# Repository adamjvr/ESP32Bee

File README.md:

# ESP32Bee
An ESP32 module in the XBee Formfactor
- XBee 2mm pitch headers, same pinout slightly modified
- ESP32 WiFi/BLE Dual Core Microcontroll/SoC
- UM Antenna Connector for external 2.4GHZ Antennas
- Open Source Hardware under CERN License
- Designed In KiCAD

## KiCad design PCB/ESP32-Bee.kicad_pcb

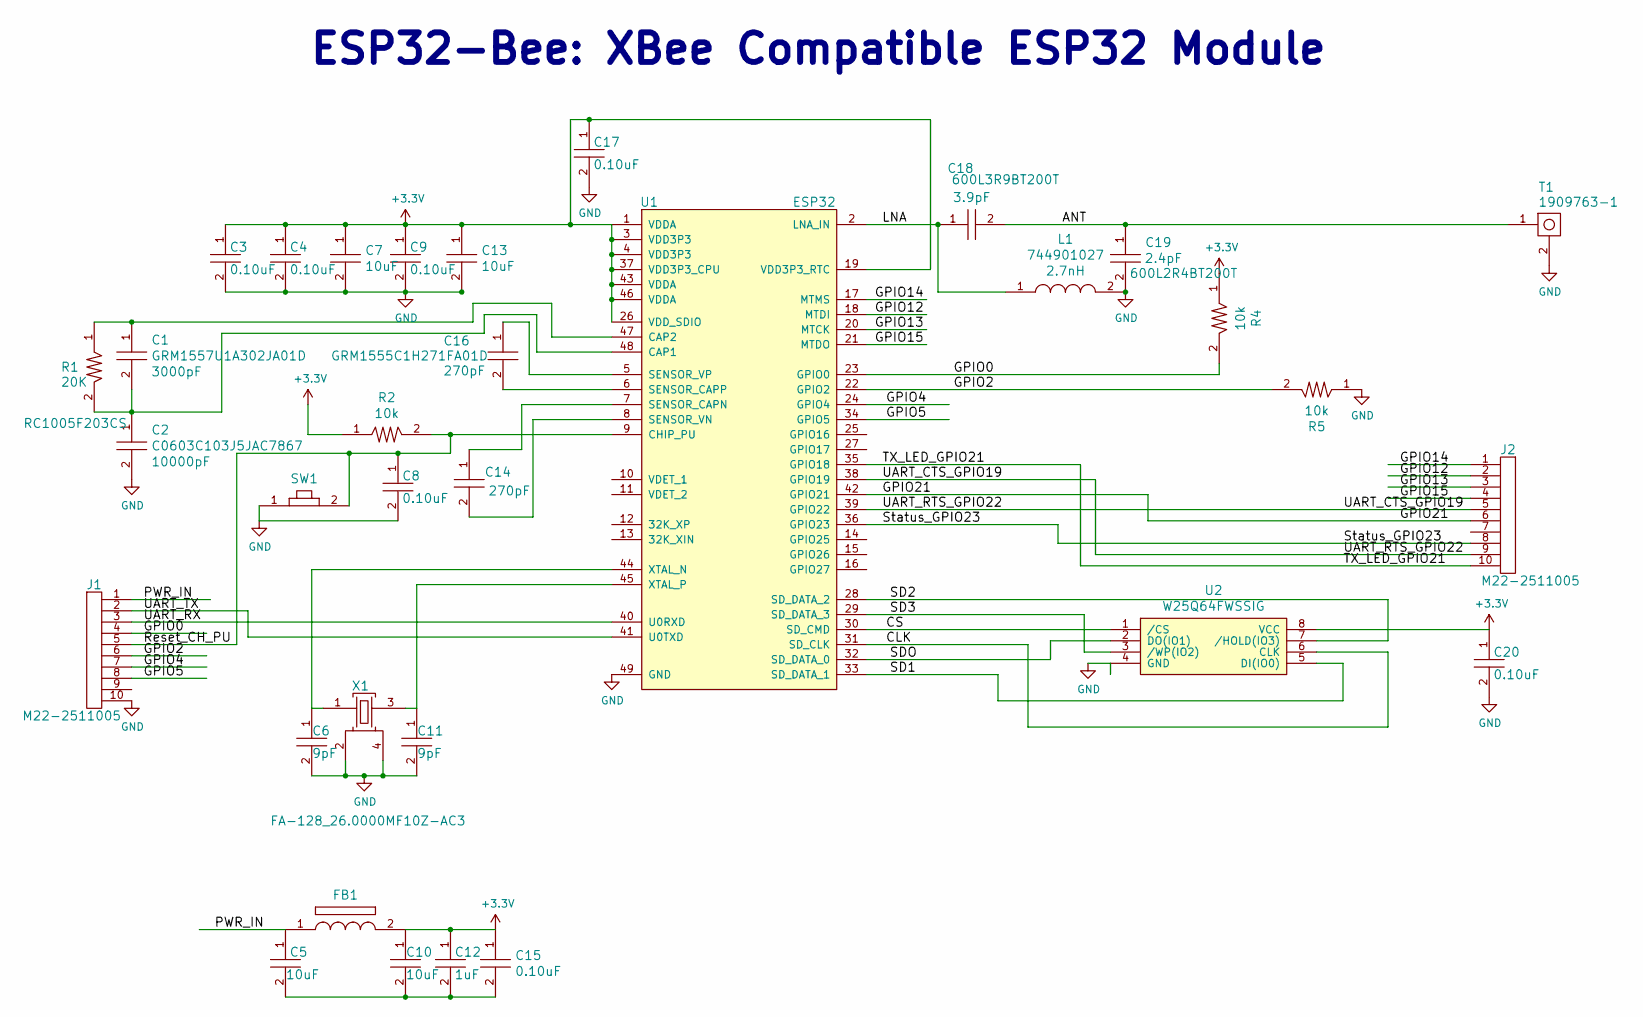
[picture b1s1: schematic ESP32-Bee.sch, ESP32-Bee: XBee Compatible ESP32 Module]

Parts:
C1: GRM1557U1A302JA01D; C0402; Tolerance 0.1pF; Voltage 10V; MFR# GRM1557U1A302JA01D
C2: C0603C103J5JAC7867; C0603; Tolerance 5%; Voltage 50V; MFR# C0603C103J5JAC7867
C3, C4, C8, C9, C15, C17, C20: CL05B104JP5NNNC; C0402; Tolerance 5%; Voltage 10V; MFR# CL05B104JP5NNNC
C5, C7, C10, C13: CL10A106KQ8NNNC; C0603; Tolerance 10%; Voltage 6.3V; MFR# CL10A106KQ8NNNC
C6, C11: CL05C090CB5NNNC; C0402; Tolerance 0.25pF; Voltage 50V; MFR# CL05C090CB5NNNC
C12: CL05A105KA5NQNC; C0402; Tolerance 10%; Voltage 25V; MFR# CL05A105KA5NQNC
C14, C16: GRM1555C1H271FA01D; C0402; Tolerance 270pF; Voltage 50V; MFR# GRM1557U1A302JA01D
C18: 600L3R9BT200T; C0402; Tolerance 0.1pF; Voltage 200V; MFR# 600L3R9BT200T
C19: 600L2R4BT200T; C0402; Tolerance 2.4pF; Voltage 200V; MFR# 600L2R4BT200T
FB1: MI0603K300R-10; Tolerance N/A; Voltage N/A; MFR# MI0603K300R-10
J1, J2: M22-2511005; Tolerance N/A; Voltage N/A; MFR# M22-2511005
L1: 744901027; BLM15HG601SN1D; Tolerance 0.1nH; Voltage N/A; MFR# 744901027
R1: RC1005F203CS; R0402; Tolerance 1%; Voltage N/A; MFR# RC1005F103CS
R2, R4, R5: RC1005F103CS; R0402; Tolerance 1%; Voltage N/A; MFR# RC1005F103CS
SW1: B3U-1000P; Tolerance %; Voltage 50V; MFR# B3U-1000P
T1: 1909763-1; Tolerance N/A; Voltage N/A; MFR# 1909763-1
U1: ESP32
U2: W25Q64FWSSIG; Tolerance N/A; Voltage 3.3V; MFR# W25Q64FWSSIG
X1: FA-128_26.0000MF10Z-AC3; Tolerance N/A; Voltage 3.3V; MFR# FA-128 26.0000MF10Z-AC3

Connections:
+3V3: C3.1, C4.1, C7.1, C9.1, C10.1, C12.1, C13.1, C15.1, C17.1, C20.1, FB1.2, R2.1, R4.1, U1.1 (VDDA), U1.3 (VDD3P3), U1.4 (VDD3P3), U1.19 (VDD3P3_RTC), U1.26 (VDD_SDIO), U1.37 (VDD3P3_CPU), U1.43 (VDDA), U1.46 (VDDA), U2.8 (VCC)
/ANT: C18.2, C19.1, T1.1
/CLK: U1.31 (SD_CLK), U2.6 (CLK)
/CS: U1.30 (SD_CMD), U2.1 (/CS)
/GPIO0: J1.4, R4.2, U1.23 (GPIO0)
/GPIO2: J1.6, R5.2, U1.22 (GPIO2)
/GPIO4: J1.7, U1.24 (GPIO4)
/GPIO5: J1.8, U1.34 (GPIO5)
/GPIO12: J2.2, U1.18 (MTDI)
/GPIO13: J2.3, U1.20 (MTCK)
/GPIO14: J2.1, U1.17 (MTMS)
/GPIO15: J2.4, U1.21 (MTDO)
/GPIO21: J2.6, U1.42 (GPIO21)
/LNA: C18.1, L1.1, U1.2 (LNA_IN)
/PWR_IN: C5.1, FB1.1, J1.1
/Reset_CH_PU: C8.1, J1.5, R2.2, SW1.2, U1.9 (CHIP_PU)
/SD1: U1.33 (SD_DATA_1), U2.5 (DI(IO0))
/SD2: U1.28 (SD_DATA_2), U2.7 (/HOLD(IO3))
/SD3: U1.29 (SD_DATA_3), U2.3 (/WP(IO2))
/SDO: U1.32 (SD_DATA_0), U2.2 (DO(IO1))
/Status_GPIO23: J2.8, U1.36 (GPIO23)
/TX_LED_GPIO21: J2.10, U1.35 (GPIO18)
/UART_CTS_GPIO19: J2.5, J2.9, U1.38 (GPIO19), U1.39 (GPIO22)
/UART_RX: J1.3, U1.40 (U0RXD)
/UART_TX: J1.2, U1.41 (U0TXD)
GND: C2.2, C3.2, C4.2, C6.2, C7.2, C8.2, C9.2, C11.2, C13.2, C17.2, C19.2, C20.2, J1.10, L1.2, R5.1, SW1.1, T1.2, U1.49 (GND), U2.4 (GND), X1.2, X1.4
unnamed: C1.1, R1.1, U1.47 (CAP2)
unnamed: C1.2, C2.1, R1.2, U1.48 (CAP1)
unnamed: C6.1, U1.44 (XTAL_N), X1.1
unnamed: C5.2, C10.2, C12.2, C15.2
unnamed: C11.1, U1.45 (XTAL_P), X1.3
unnamed: C14.1, U1.7 (SENSOR_CAPN)
unnamed: C14.2, U1.8 (SENSOR_VN)
unnamed: C16.1, U1.5 (SENSOR_VP)
unnamed: C16.2, U1.6 (SENSOR_CAPP)

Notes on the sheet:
ESP32-Bee: XBee Compatible ESP32 Module

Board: 2 copper layers, 33 parts (0 on the bottom side), 35 nets, no tracks yet.

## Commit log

2016-10-21 Schematic
    Schematic completed, PCB started and baord outline added to edge cuts
    layer.
2016-10-31 More Progress
    More progress with the PCB, having a hard time finding a RF shielf that
    is XBee pro sized.
